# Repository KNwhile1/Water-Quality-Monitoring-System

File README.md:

# Project-PPS

# Water Quality Measurement Device for Lakes or Rivers with Geolocation, Connected to the Internet (Cloud)

## Context and Origin
Our company specializes in manufacturing devices to measure water quality in lakes and rivers. Traditionally, our teams travel by boat to take measurements on-site and collect water samples for laboratory analysis. Each measurement includes data on the date, time, temperature, geographical location, and water sample, all recorded on paper. One employee had the innovative idea of creating a device that would automatically take measurements and record data without the need for paper notes or water samples. This device would allow real-time water quality measurements and instantly send the data to our databases to be visualized on a Google Maps map, offering up-to-date accessibility for everyone.

In order to bring this vision to life and continue our commitment to environmental health, we have decided to develop and commercialize this product, which will replace our current methods.

## General Need
The required device is a water quality measurement system capable of collecting and transmitting data on the concentration of certain gases (such as oxygen) and water temperature. It must include geolocation, battery level, and send the data to a cloud platform via the LoRaWAN network. The data should be displayed on a Google Maps map.

## Objectives
- Design a device capable of measuring water quality
- Transmit the collected data to a cloud platform accessible by employees
- Display water quality data on a Google Maps map in real-time
- Key Functions

## The device can
- Measure oxygen (O2) concentration in the water
- Measure water temperature
- Provide geolocation data (latitude and longitude), as well as the date and time of the measurement
- Indicate voltage and battery level
- Send the collected data via the LoRaWAN network to a cloud platform (ThingsBoard)
- Update data every 5 minutes
- Display the collected data on an integrated Google Maps map on the ThingsBoard platform

## Required Components (images)
- Maduino Zero LoRaWAN

- Waterproof 1-WIRE temperature sensor (5V)

- Waterproof oxygen concentration sensor (5V)

- 1K Ohm 1206 resistor

- 2 AA 1.5V batteries

- Battery holder for 2 AA batteries

- On/Off switch to control power

- 3.3V to 5V boost converter

*See the **Project Purchase Links** category for purchase links*

## Conclusion
This project aims to revolutionize how we measure and track the water quality of lakes and rivers. With this device, we will be able to provide precise, instant, and accessible data to our entire team while ensuring improved environmental monitoring.

*Representation of the project assembly*

# Functional File Versions for this Project
- /Codes/CodeV1.3 ---> **CodeV1.3.ino**
- /3D_Prints/Boiter3DV1.1 ---> **PPS_Boitier.stl** and **PPS_CouvercleBoitier.stl**
- /Schematics/CircuitV1.3 ---> **PPS_schematic.sch**
- /Schematics/MatrixV1.3 ---> **PPS_schematic.brd**

# Problems Encountered
See /Problem_List ---> Liste_problemes_PPS.xlsx

# Project Purchase Links
See /Component_List ---> Liste_composants_PPS.xlsx

# Additional Information Links
- [CayenneLPP](https://github.com/myDevicesIoT/CayenneLPP)
- [Arduino LoRaWAN Device Library](https://github.com/TheThingsNetwork/arduino-device-lib)
- [ASR650X AT Command Introduction](https://www.hoperf.com/data/upload/back/20190605/ASR650X%20AT%20Command%20Introduction-20190605.pdf)
- [Maduino Zero LoRaWAN](https://github.com/Makerfabs/Maduino-Zero-Lorawan/tree/Ra07)
- [Github chirpstack docker](https://github.com/chirpstack/chirpstack-docker)
- [ChirpStack Documentation](https://www.chirpstack.io/docs/)
- [ThingsBoard Documentation](https://thingsboard.io/)

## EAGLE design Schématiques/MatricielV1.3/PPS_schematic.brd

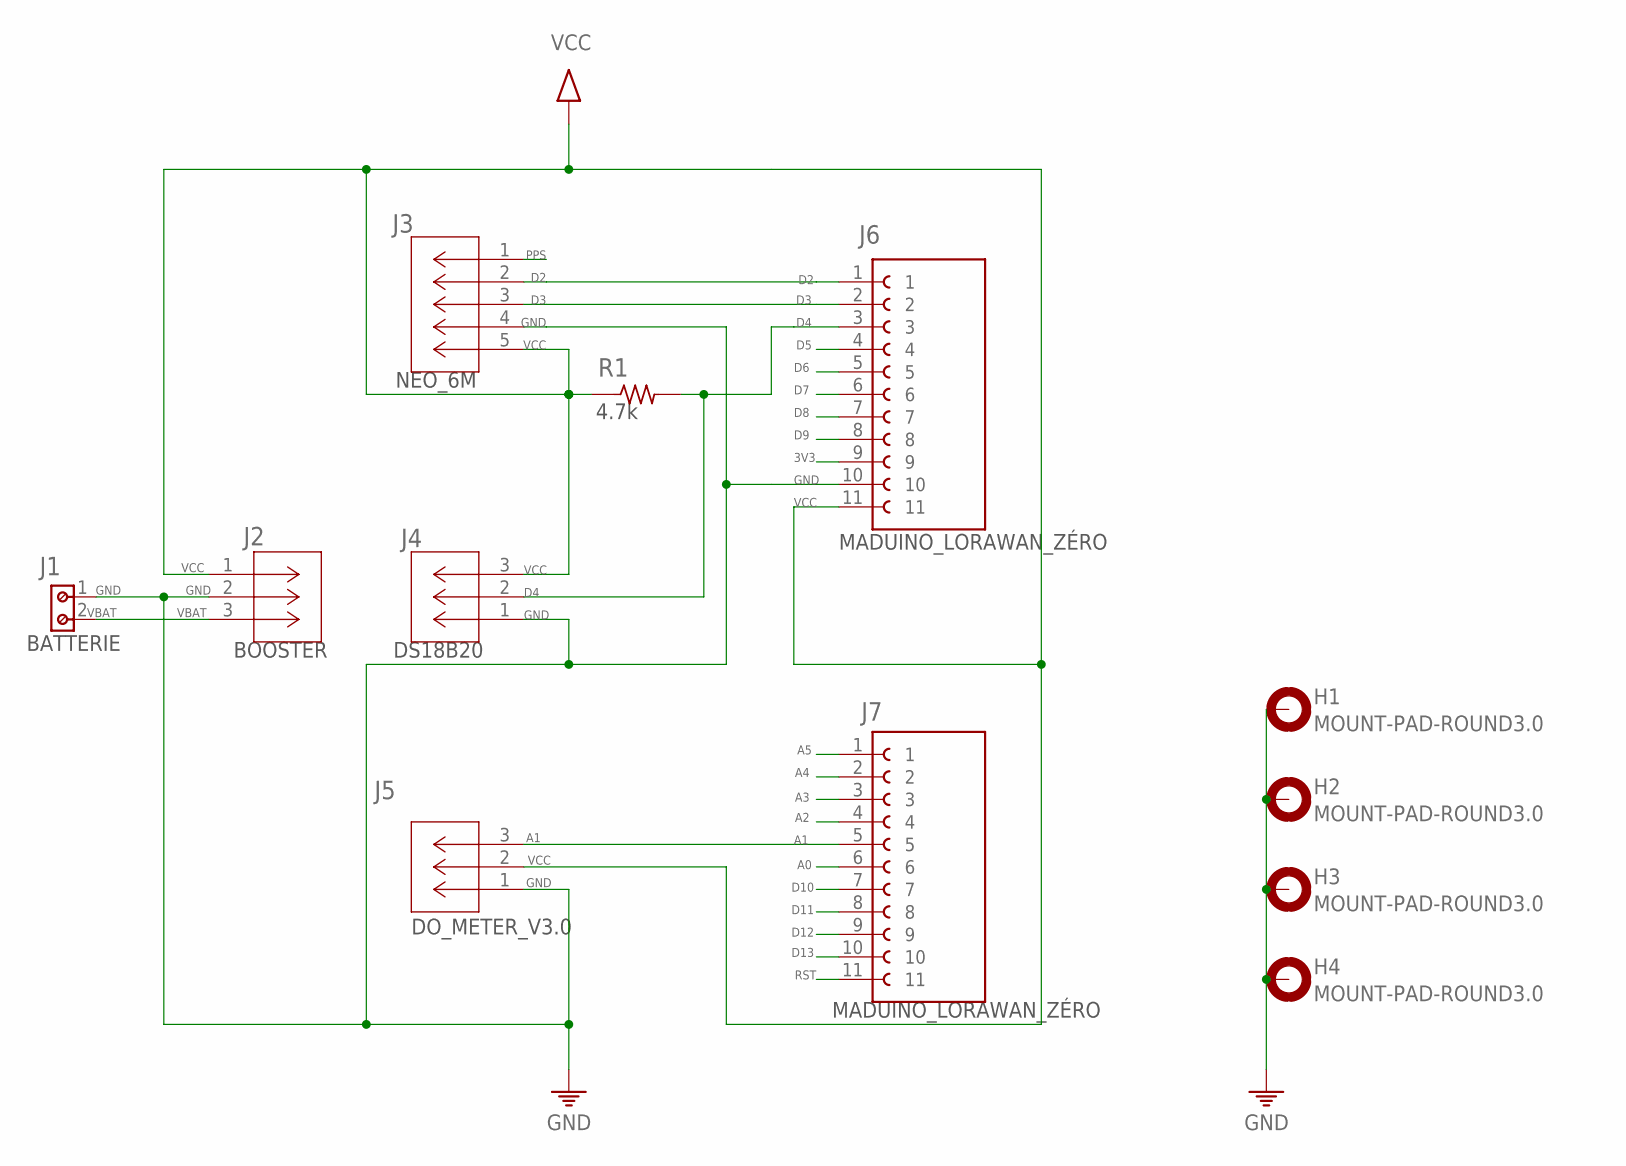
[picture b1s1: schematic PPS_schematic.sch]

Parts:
H1, H2, H3, H4: MOUNT-PAD-ROUND3.0; 3,0-PAD
J1: Batterie; 691137710002
J2: BOOSTER; CON3_1X3_TU_HTS_SAI
J3: NEO-6M; CONN5_1LFBN-RC_SUL
J4: DS18B20; CONN_PPTC031_SUL
J5: D0_METTER_v3.0; CONN_PPTC031_SUL
J6, J7: MADUINO_LORAWAN_ZÉRO; HARWIN_M20-7821146
R1: 4.7k; M1206

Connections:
3V3: J6.9
A1: J5.3, J7.5
A2: J7.4
A3: J7.3
A4: J7.2
A5: J7.1
D2: J3.2, J6.1
D3: J3.3, J6.2
D4: J4.2, J6.3, R1.2
D5: J6.4
D6: J6.5
D7: J6.6
D8: J6.7
D9: J6.8
D10: J7.7
D11: J7.8
D12: J7.9
D13: J7.10
GND: H1.B3,0, H2.B3,0, H3.B3,0, H4.B3,0, J1.1, J2.2, J3.4, J4.1, J5.1, J6.10
PPS: J3.1
RST: J7.11
VBAT: J1.2, J2.3

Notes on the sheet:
BOOSTER
DS18B20
DO_METER_V3.0
NEO_6M
BATTERIE
MADUINO_LORAWAN_ZÉRO

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
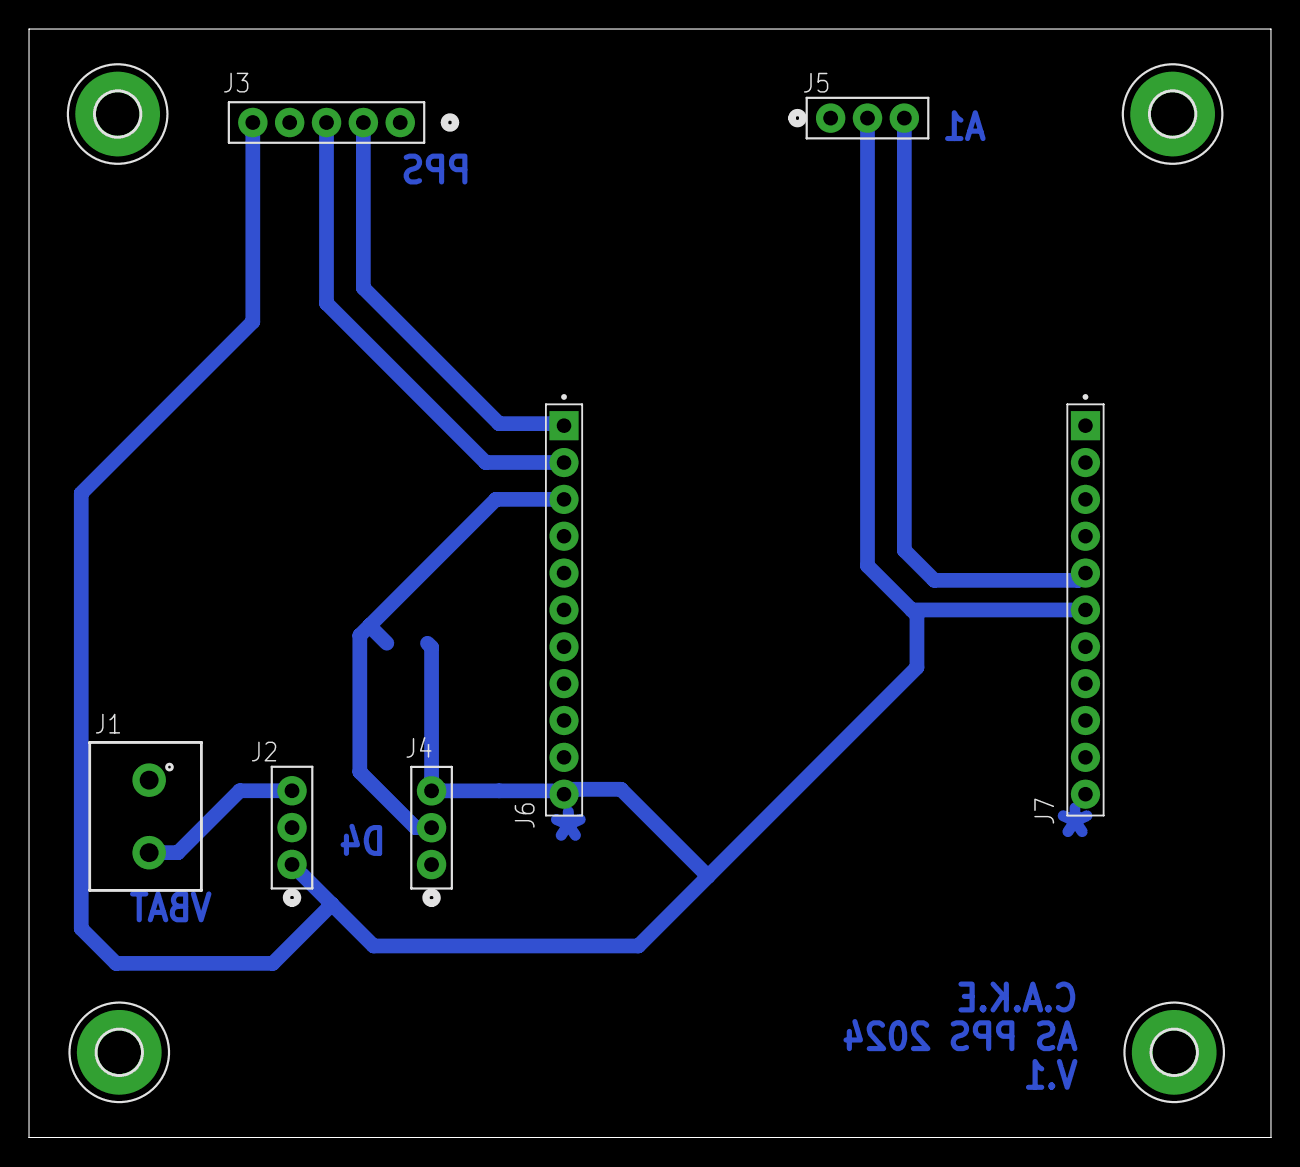
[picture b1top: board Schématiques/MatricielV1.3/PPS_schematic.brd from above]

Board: 2 copper layers, 85.6 x 76.4 mm, 12 parts (1 on the bottom side), 7 nets.

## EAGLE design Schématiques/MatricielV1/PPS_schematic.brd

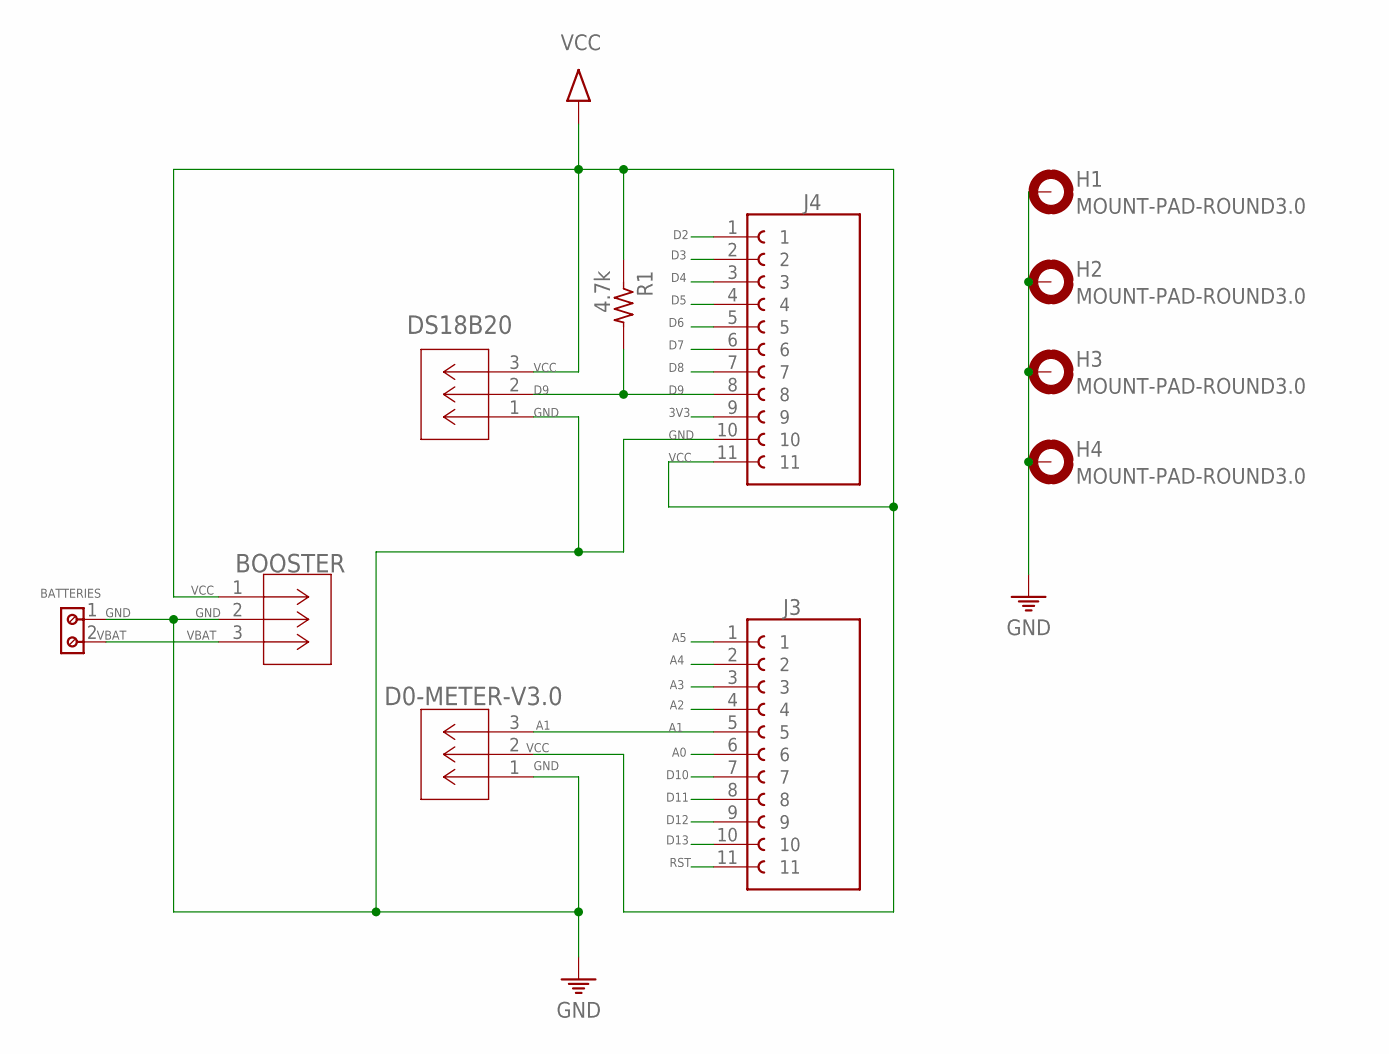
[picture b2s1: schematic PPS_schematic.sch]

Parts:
BATTERIES: 691137710002
BOOSTER: TS-103-T-ACON3_1X3_TU_HTS_SAI; CON3_1X3_TU_HTS_SAI
D0-METER-V3.0: PPTC031LFBN-RCCONN_PPTC031_SUL; CONN_PPTC031_SUL
DS18B20: PPTC031LFBN-RCCONN_PPTC031_SUL; CONN_PPTC031_SUL
H1, H2, H3, H4: MOUNT-PAD-ROUND3.0; 3,0-PAD
J3, J4: M20-7821146; HARWIN_M20-7821146
R1: 4.7k; M1206

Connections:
3V3: J4.9
A0: J3.6
A1: D0-METER-V3.0.3, J3.5
A2: J3.4
A3: J3.3
A4: J3.2
A5: J3.1
D2: J4.1
D3: J4.2
D4: J4.3
D5: J4.4
D6: J4.5
D7: J4.6
D8: J4.7
D9: DS18B20.2, J4.8, R1.2
D10: J3.7
D11: J3.8
D12: J3.9
D13: J3.10
GND: BATTERIES.1, BOOSTER.2, D0-METER-V3.0.1, DS18B20.1, H1.B3,0, H2.B3,0, H3.B3,0, H4.B3,0, J4.10
RST: J3.11
VBAT: BATTERIES.2, BOOSTER.3
VCC: BOOSTER.1, D0-METER-V3.0.2, DS18B20.3, J4.11, R1.1

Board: 2 copper layers, 11 parts (0 on the bottom side), 5 nets, no tracks yet.

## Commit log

2024-10-31 Create q
2024-11-06 Create qq
2024-11-07 Create MatricielV3
2024-11-13 Rename download5.png to download6.png

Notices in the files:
parts and their libraries:
2024-10-23_16-02-51_Library: COPYRIGHT: Copyright (C) 2024 Ultra Librarian. All rights reserved.
